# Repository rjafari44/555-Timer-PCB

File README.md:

# 555 Timer Astable PCB

## Overview
This PCB is a simple **555 timer** circuit configured in **astable mode**, designed to blink an LED. It is powered by a 9V battery and includes a single LED with a current-limiting resistor. 

This was a project done under IEEE at UC Irvine. The PCB was designed using **KiCad**.  

Key features:  

- Uses **NE555 or equivalent** timer IC  
- Astable configuration for continuous oscillation  
- Battery-powered (9V)  
- LED indicator with current-limiting resistor  
- LTSpice simulation file included for testing and verification  

---

## Components
- **Timer IC:** 555 timer (NE555)  
- **Capacitor:** 1µF between TRIG/THRES and GND  
- **Resistors:**  
  - R1 = 1kΩ series resistor with LED 
  - R2 = 470kΩ between DISCH and TRIG/THRES  
  - R3 = 1kΩ between DISCH and VCC node (also RESET tied to VCC)
- **LED:** Indicator for output  
- **Power supply:** 9V battery  

---

## Wiring & Connections
| Pin | Connection |
|-----|-----------|
| VCC | Positive battery terminal (+9V) |
| GND | Negative battery terminal |
| DISCH | Connected through R3 (1kΩ) to VCC node |
| TRIG | Connected to R2 (470kΩ) from DISCH and 1µF capacitor to GND |
| THRES | Connected to TRIG and 1µF capacitor to GND |
| OUT | LED in series with R1 (1kΩ) to GND |
| RESET | Tied to VCC node (battery positive) |
| CV | Disconnected |

> The LED includes a built-in 1kΩ current-limiting resistor.  
> **Note:** The battery connector is where you connect the 9V battery; observe LED polarity.

---

## Usage
1. Connect a 9V battery to the PCB.  
2. The 555 timer begins oscillating in astable mode.  
3. The LED will blink according to the calculated frequency.  
4. You can simulate the circuit using the included LTSpice file to verify timing and LED behavior.  

---

## Calculations

For a 555 timer in astable mode:

```
T_high = 0.693 * (R2 + R3) * C
T_low  = 0.693 * R2 * C
T_total = T_high + T_low = 0.693 * (R3 + 2*R2) * C
f = 1 / T_total
Duty cycle = T_high / T_total
```

**Using component values:**  

- R2 = 470kΩ  
- R3 = 1kΩ  
- C = 1µF  

**Step 1: Total period**  

```
T_total = 0.693 * (R3 + 2*R2) * C
T_total = 0.693 * (1,000 + 2*470,000) * 0.000001
T_total ≈ 0.651 seconds
```

**Step 2: Frequency**  

```
f = 1 / T_total ≈ 1 / 0.651 ≈ 1.54 Hz
```

**Step 3: Duty cycle**  

```
T_high = 0.693 * (R2 + R3) * C
T_high = 0.693 * (470,000 + 1,000) * 0.000001 ≈ 0.326 s
Duty cycle ≈ T_high / T_total ≈ 0.326 / 0.651 ≈ 50%
```

> R1 (LED resistor) does not affect timing.

---

## Simulation
- You can simulate the circuit using the included **LTSpice file**.  
- The OUT pin waveform will correspond to the LED blink pattern.  
- Adjust R2, R3, or C to change the frequency and duty cycle as needed.  

---

## Images

### Schematic

### PCB Layout

### 3D PCB Render

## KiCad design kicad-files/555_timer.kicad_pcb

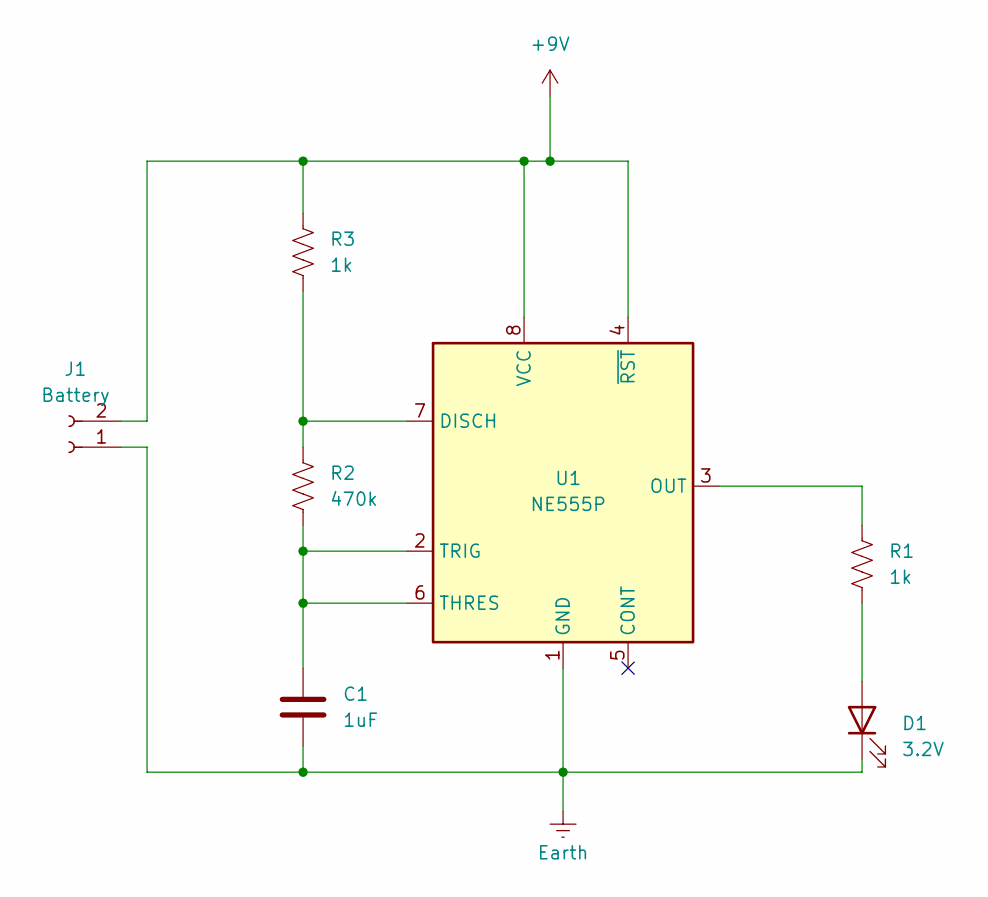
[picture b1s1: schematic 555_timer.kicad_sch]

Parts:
C1: 1uF; CP_Radial_D4.0mm_P2.00mm
D1: 3.2V; LED_D3.0mm
J1: Battery; PinHeader_1x02_P2.54mm_Vertical
R1, R3: 1k; R_Axial_DIN0207_L6.3mm_D2.5mm_P7.62mm_Horizontal
R2: 470k; R_Axial_DIN0207_L6.3mm_D2.5mm_P7.62mm_Horizontal
U1: NE555P; DIP-8_W7.62mm

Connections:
+9V: J1.2, R3.1, U1.4 (~RST), U1.8 (VCC)
Earth: C1.2, D1.1 (K), J1.1, U1.1 (GND)
unnamed: D1.2 (A), R1.2
unnamed: R2.2, R3.2, U1.7 (DISCH)
unnamed: R1.1, U1.3 (OUT)
unnamed: C1.1, R2.1, U1.2 (TRIG), U1.6 (THRES)

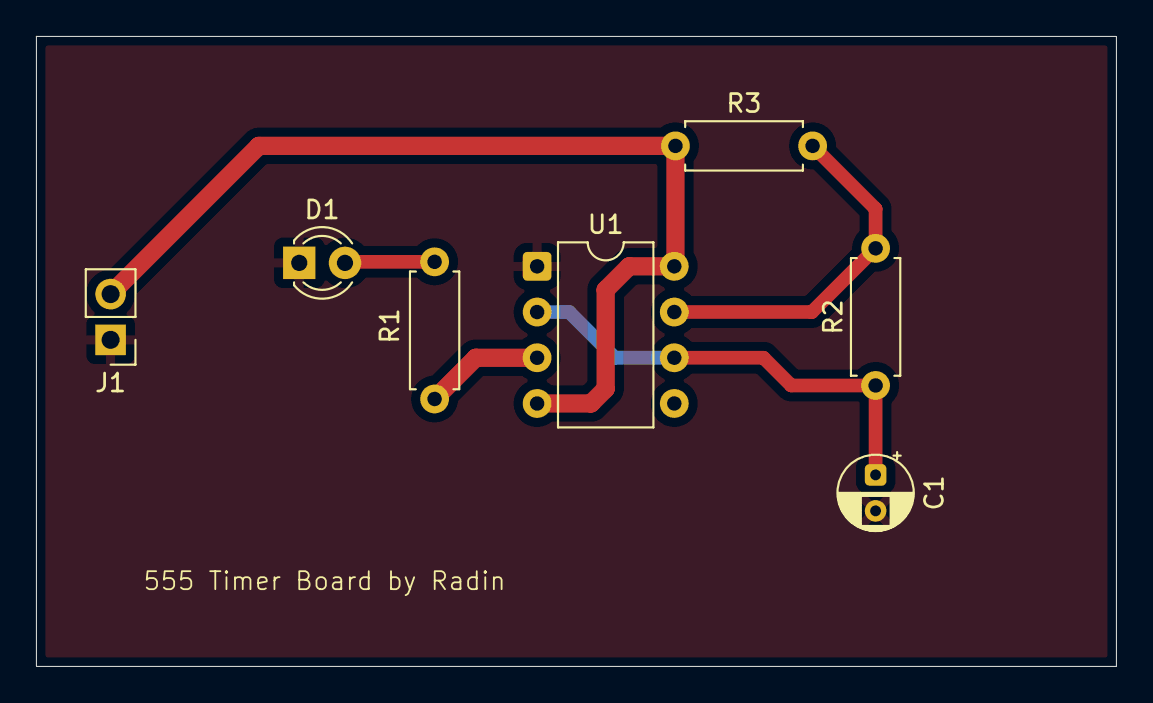
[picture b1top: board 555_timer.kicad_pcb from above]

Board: 2 copper layers, 60.0 x 35.0 mm, 7 parts (0 on the bottom side), 6 nets.

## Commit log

2026-03-31 uploaded kicad and ltspice files
2026-03-31 added images
2026-03-31 updated README, ltspice file and renamed images
2026-04-19 renamed images and updated README
